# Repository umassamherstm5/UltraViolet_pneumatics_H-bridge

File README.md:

UltraViolet_pneumatics_H-bridge
===============================

Schematic and board to control solenoid valves which in turn control the pneumatic raising and lowering of UltraViolet's platform

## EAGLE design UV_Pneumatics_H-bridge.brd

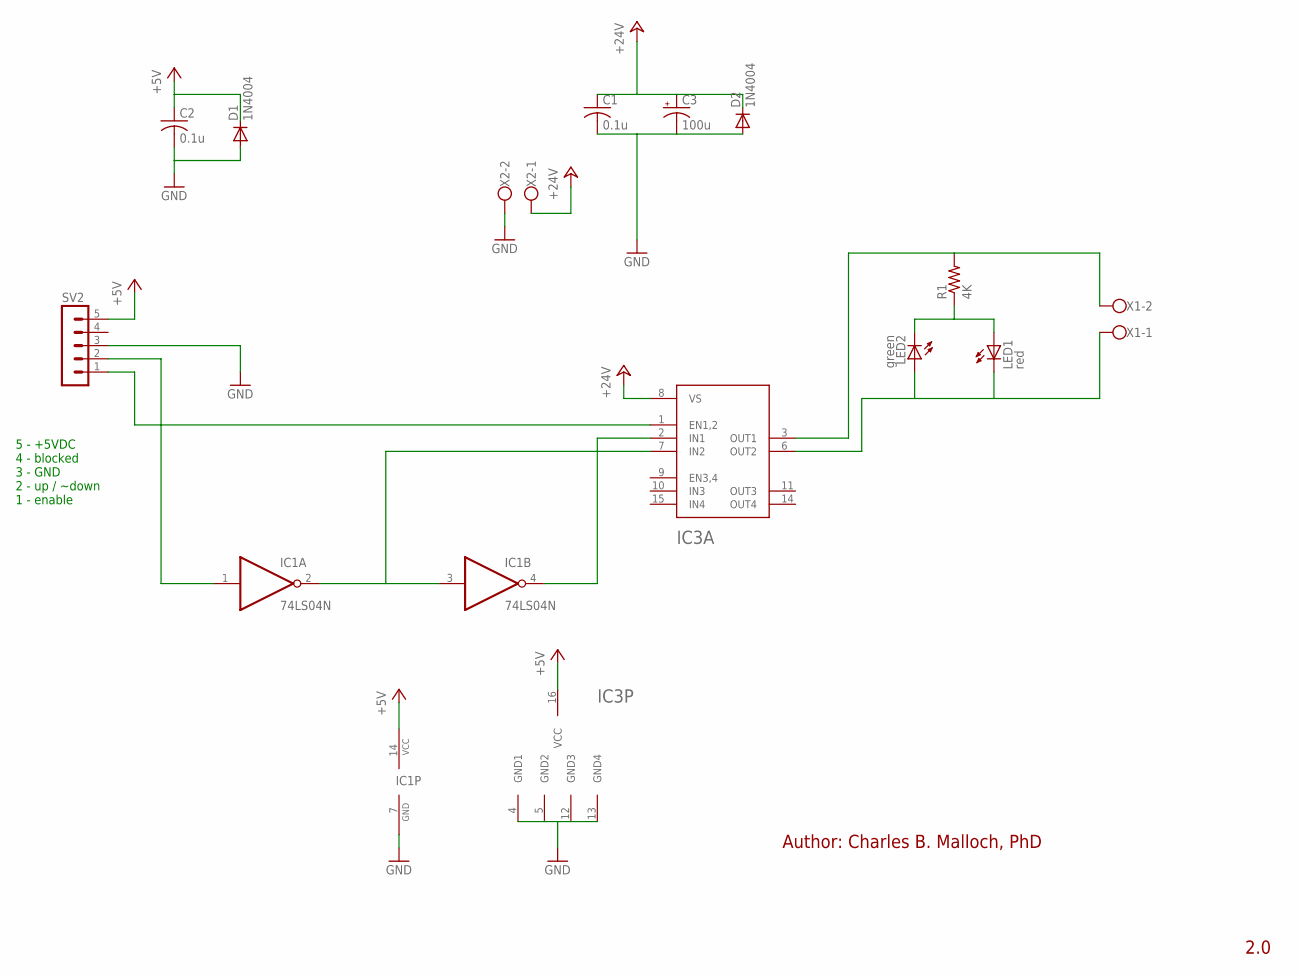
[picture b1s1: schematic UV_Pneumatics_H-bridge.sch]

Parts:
C1, C2: 0.1u; C025-025X050
C3: 100u; E3,5-10
D1, D2: 1N4004; DO41-10
IC1: 74LS04N; DIL14
IC3: L293D; DIP16
LED1: red; LED3MM
LED2: green; LED3MM
R1: 4K; 0207/10
SV2: MA05-1
X1, X2: W237-102

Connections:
+5V: C2.1, D1.C, IC1.14 (VCC), IC3.16 (VCC), SV2.5
+24V: C1.1, C3.+, D2.C, IC3.8 (VS), X2.1
GND: C1.2, C2.2, C3.-, D1.A, D2.A, IC1.7 (GND), IC3.4 (GND1), IC3.5 (GND2), IC3.12 (GND3), IC3.13 (GND4), SV2.3, X2.2
unnamed: IC1.1 (I), SV2.2
unnamed: IC1.2 (O), IC1.3 (I), IC3.7 (IN2)
unnamed: IC1.4 (O), IC3.2 (IN1)
unnamed: IC3.1 (EN1,2), SV2.1
unnamed: LED1.A, LED2.K (C), R1.1
unnamed: IC3.3 (OUT1), R1.2, X1.2
unnamed: IC3.6 (OUT2), LED1.K (C), LED2.A, X1.1

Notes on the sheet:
5 - +5VDC 4 - blocked 3 - GND 2 - up / ~down 1 - enable
Author: Charles B. Malloch, PhD
2.0

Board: 2 copper layers, 13 parts (0 on the bottom side), 10 nets, no tracks yet.

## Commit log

2014-10-09 Created schematic and board layout
2014-10-15 Updated schematic with Author and Version data
    No substantive changes
2014-10-15 V2.0
    As built. Replaced 74LS06 with 74LS04, which is TTL as intended
